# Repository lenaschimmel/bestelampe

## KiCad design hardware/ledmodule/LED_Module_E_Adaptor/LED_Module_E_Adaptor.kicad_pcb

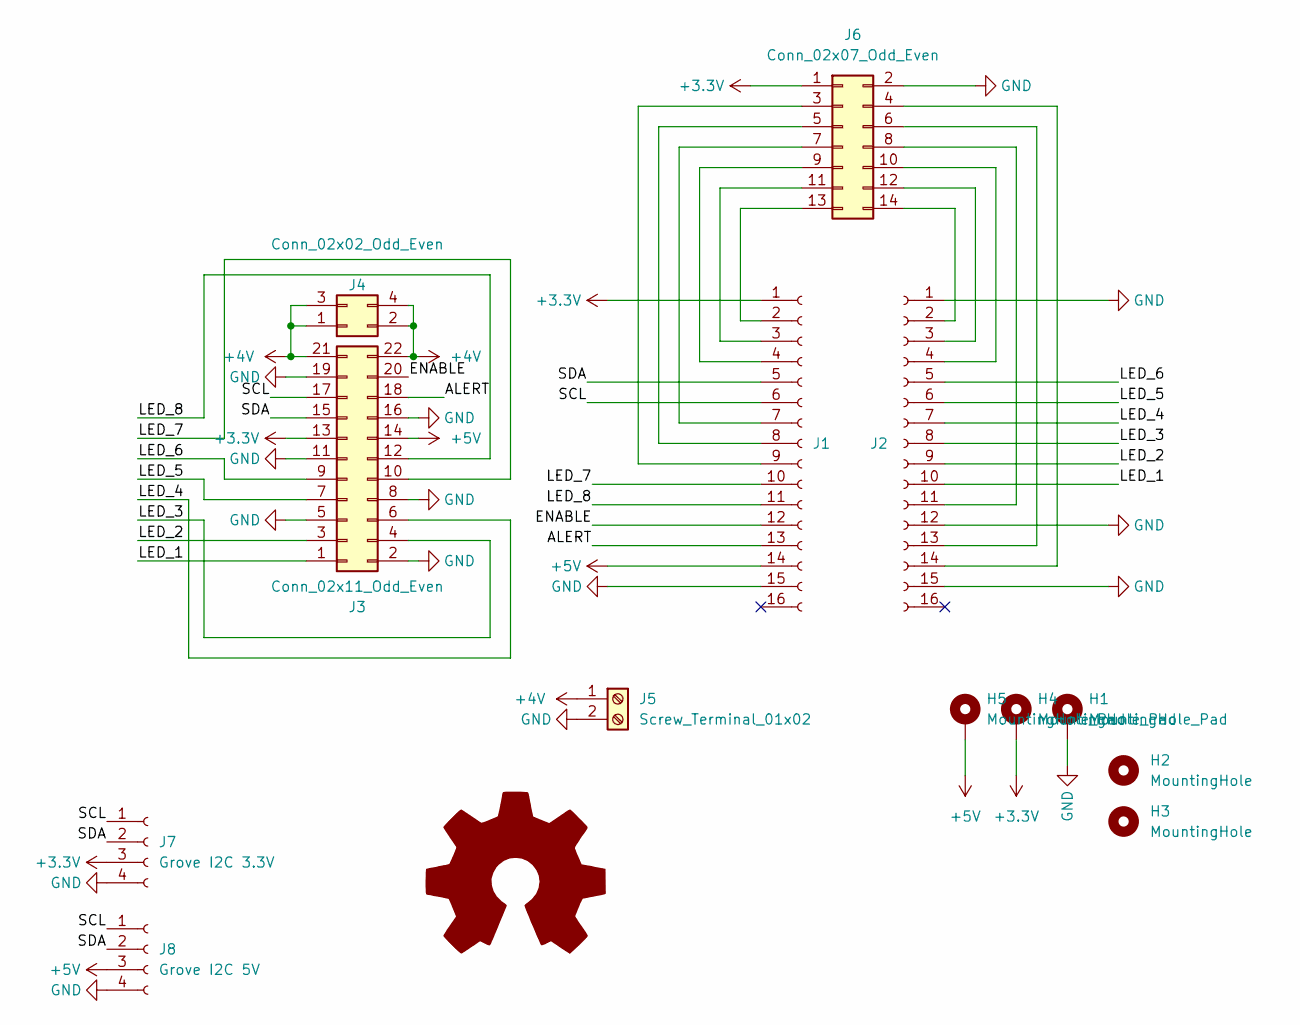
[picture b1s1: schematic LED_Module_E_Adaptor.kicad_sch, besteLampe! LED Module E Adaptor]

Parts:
H1, H4, H5: MountingHole_Pad; TestPoint_THTPad_D2.5mm_Drill1.2mm
H2, H3: MountingHole; MountingHole_3.2mm_M3
J1, J2: Conn_01x16_Socket; PinSocket_1x16_P2.54mm_Vertical
J3: Conn_02x11_Odd_Even; PinHeader_2x11_P2.54mm_Vertical
J4: Conn_02x02_Odd_Even; PinHeader_2x02_P2.54mm_Vertical
J5: Screw_Terminal_01x02; TerminalBlock_4Ucon_1x02_P3.50mm_Horizontal
J6: Conn_02x07_Odd_Even; PinHeader_2x07_P2.54mm_Vertical
J7: Grove I2C 3.3V; NS-Tech_Grove_1x04_P2mm_Vertical
J8: Grove I2C 5V; NS-Tech_Grove_1x04_P2mm_Vertical

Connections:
+3.3V: H4.1, J1.1, J3.13, J6.1, J7.3
+4V: J3.21, J3.22, J4.1, J4.2, J4.3, J4.4, J5.1
+5V: H5.1, J1.14, J3.14, J8.3
/ALERT: J1.13, J3.18
/ENABLE: J1.12, J3.20
/LED_1: J2.10, J3.1
/LED_2: J2.9, J3.3
/LED_3: J2.8, J3.4
/LED_4: J2.7, J3.6
/LED_5: J2.6, J3.7
/LED_6: J2.5, J3.9
/LED_7: J1.10, J3.10
/LED_8: J1.11, J3.12
/SCL: J1.6, J3.17, J7.1, J8.1
/SDA: J1.5, J3.15, J7.2, J8.2
GND: H1.1, J1.15, J2.1, J2.12, J2.15, J3.2, J3.5, J3.8, J3.11, J3.16, J3.19, J5.2, J6.2, J7.4, J8.4
unnamed: J1.2, J6.13
unnamed: J1.3, J6.11
unnamed: J1.4, J6.9
unnamed: J1.7, J6.7
unnamed: J1.8, J6.5
unnamed: J1.9, J6.3
unnamed: J2.2, J6.14
unnamed: J2.3, J6.12
unnamed: J2.4, J6.10
unnamed: J2.11, J6.8
unnamed: J2.13, J6.6
unnamed: J2.14, J6.4

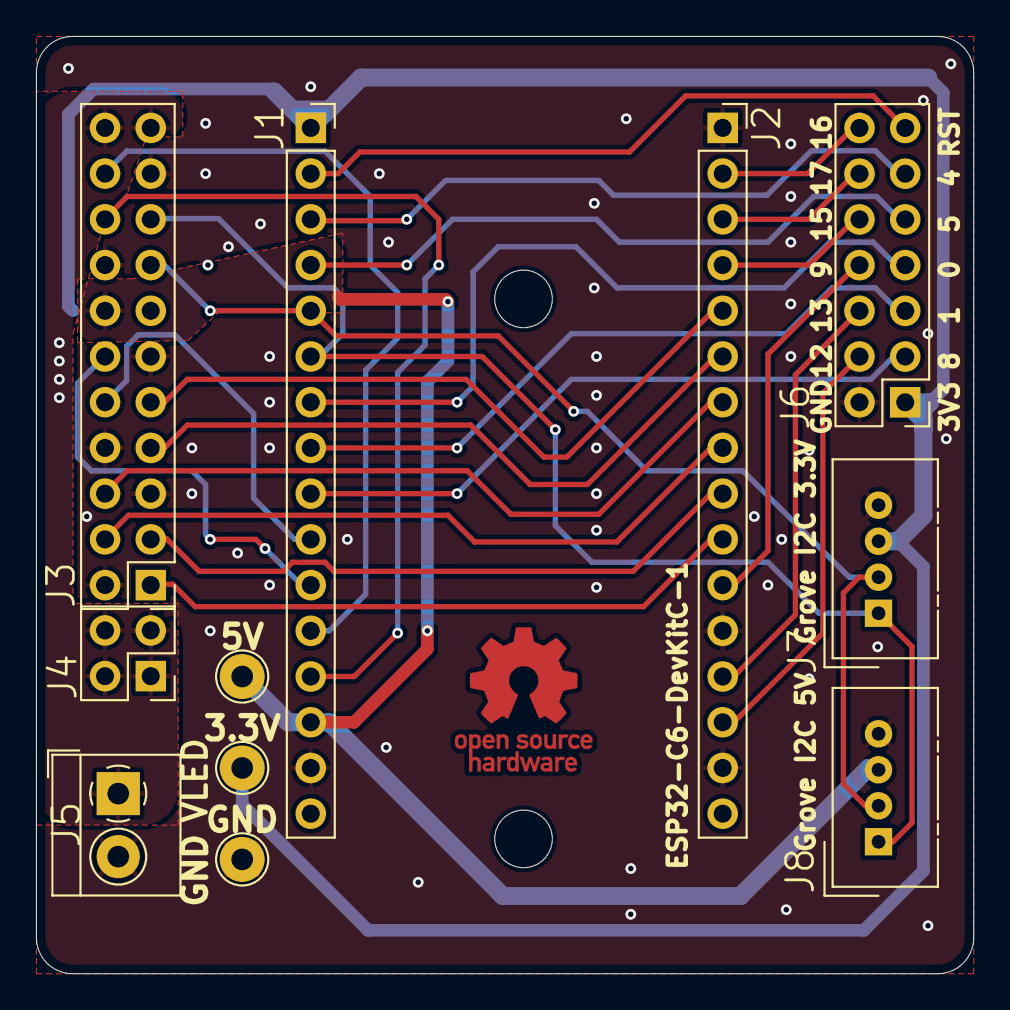
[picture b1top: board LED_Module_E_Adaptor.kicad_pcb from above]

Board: 2 copper layers, 52.1 x 52.1 mm, 13 parts (0 on the bottom side), 28 nets.

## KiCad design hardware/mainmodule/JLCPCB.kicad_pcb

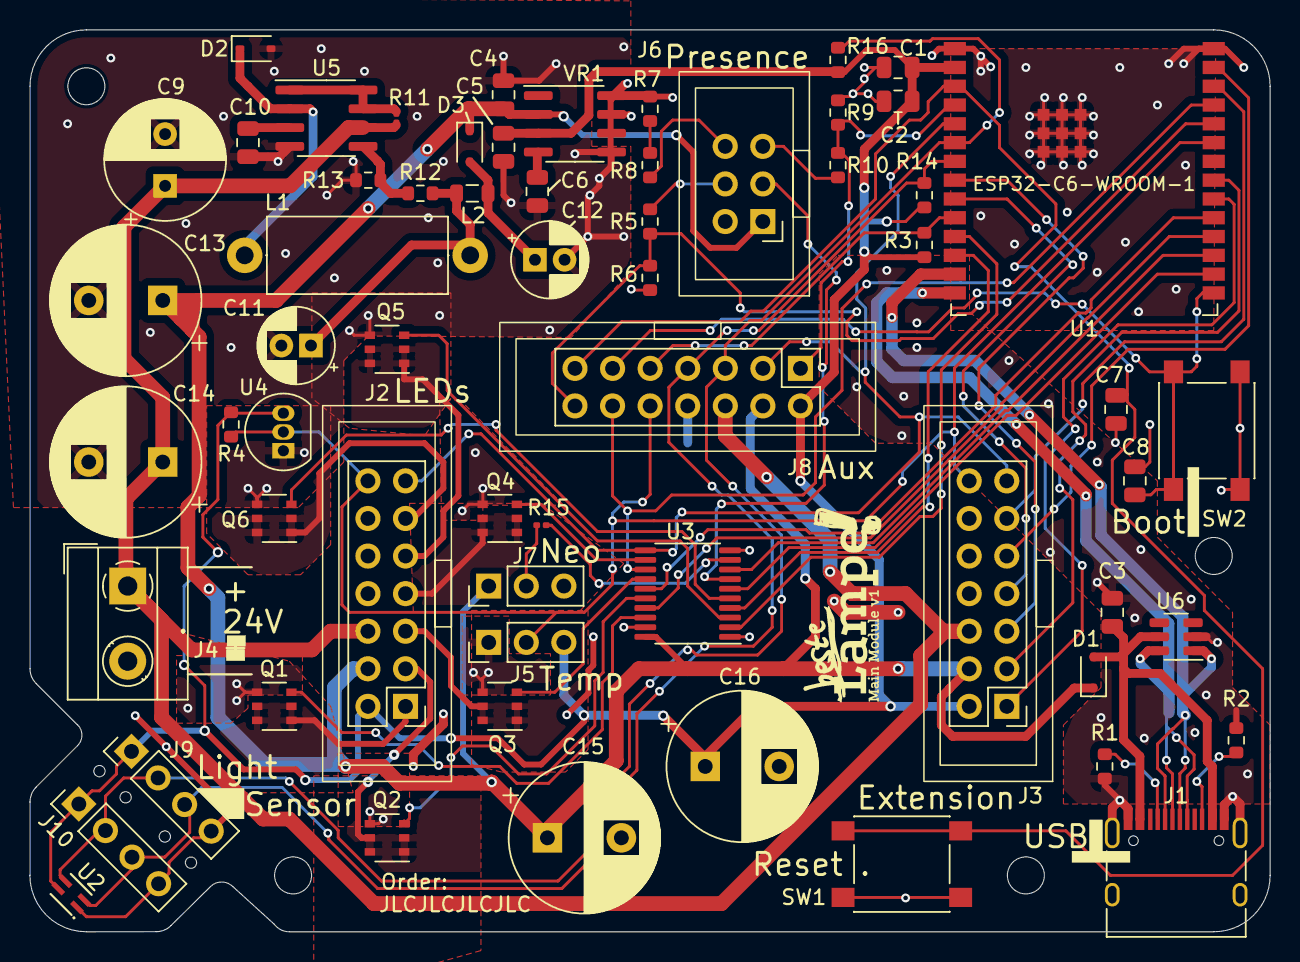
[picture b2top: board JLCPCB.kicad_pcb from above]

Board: 2 copper layers, 83.8 x 61.0 mm, 65 parts (0 on the bottom side), 57 nets.

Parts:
C1, C7, C8: 100n; C_0805_2012Metric
C2: 22u; C_0805_2012Metric
C3: 10u; C_0805_2012Metric
C4: 1u; C_0805_2012Metric
C5: 2u2; C_0805_2012Metric
C6: 10n; C_0805_2012Metric
C9: 100u; CP_Radial_D8.0mm_P3.50mm
C10: 470p; C_0805_2012Metric
C11: 2u2; CP_Radial_D5.0mm_P2.00mm
C12: 100u; CP_Radial_D5.0mm_P2.00mm
C13, C14, C15, C16: 470u; CP_Radial_D10.0mm_P5.00mm
D1, D2, D3: 1N5819; D_SOD-323
H1, H1#2, H1#3, H1#4: MountingHole; MountingHole_2.5mm
J1: USB+; USB_C_Receptacle_HRO_TYPE-C-31-M-12
J2: To LED_MOD_0; PinHeader_2x07_P2.54mm_Vertical_Boxed
J3: To EXT_MOD_1; PinHeader_2x07_P2.54mm_Vertical_Boxed
J4: V24_IN; TerminalBlock_MetzConnect_Type101_RT01602HBWC_1x02_P5.08mm_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
J5: Temp; PinHeader_1x03_P2.54mm_Vertical
J6: Presence; PinHeader_2x03_P2.54mm_Vertical_Boxed
J7: Neo; PinHeader_1x03_P2.54mm_Vertical
J8: AUX; PinHeader_2x07_P2.54mm_Vertical_Boxed
J9, J10: Conn_01x04; PinHeader_1x04_P2.54mm_Vertical
L1: 220u; L_Axial_L12.0mm_D5.0mm_P15.24mm_Horizontal_Fastron_MISC
L2: 1u; L_0805_2012Metric
Q1, Q2, Q3, Q4, Q5, Q6: Si3456DDV; TSOP-6_1.65x3.05mm_P0.95mm
R1, R2, R4, R5, R8, R10: 5K1; R_0603_1608Metric
R3, R6, R7, R9: 10K; R_0603_1608Metric
R11: 360m; R_0201_0603Metric
R12: 22k; R_0603_1608Metric
R13: 6k8; R_0603_1608Metric
R14, R16: 2k4; R_0603_1608Metric
R15: 470; R_0201_0603Metric
SW1, SW2: SW_Push; SW_Push_1P1T_NO_6x6mm_H9.5mm
U1: ESP32-C6-WROOM-1
U3: 74HCT244; TSSOP-20_4.4x6.5mm_P0.65mm
U4: DS18B20; TO-92_Inline
U5: MC34063AD; SOIC-8_3.9x4.9mm_P1.27mm
U6: DT1042-04SO1; TSOT-23-6
VR1: 3V3; SOIC-8_3.9x4.9mm_P1.27mm

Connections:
+3.3V: C1.1, C2.1, C5.1, C16.1, J2.2, J3.2, J5.3, J8.2, J9.1, J10.1, R3.2, R4.1, R14.2, R16.2, U1.2 (3V3), U4.3 (V_{DD}), VR1.3 (VOUT)
+5V: C4.1, C13.1, C15.1, D1.1 (K), D3.1 (K), J2.4, J3.4, J6.1, J7.1, J8.4, U3.20 (VCC), VR1.2 (VIN)
+24V: C9.1, C14.1, J2.6, J3.6, J4.1, J8.6, R11.1, U5.6 (Vin)
/BOOT8: J8.9, R3.1, U1.10 (GPIO8)
/BOOT9: C8.2, J8.11, SW2.2, U1.15 (GPIO9)
/CC1: J1.A5 (CC1), R1.1
/CC2: J1.B5 (CC2), R2.1
/CH0.1: U1.11 (GPIO10), U3.2 (1A0)
/CH0.2: U1.12 (GPIO11), U3.4 (1A1)
/CH0.3: U1.16 (GPIO18), U3.6 (1A2)
/CH0.4: U1.17 (GPIO19), U3.8 (1A3)
/CH0.5: U1.18 (GPIO20), U3.17 (2A0)
/CH0.6: U1.19 (GPIO21), U3.15 (2A1)
/D+: J1.A6 (D+), J1.B6 (D+), U1.14 (GPIO13/USB_D+), U6.6 (IO4)
/D-: J1.A7 (D-), J1.B7 (D-), U1.13 (GPIO12/USB_D-), U6.1 (IO1)
/DR0.1: Q1.3 (G), U3.18 (1Y0)
/DR0.2: Q2.3 (G), U3.16 (1Y1)
/DR0.3: Q3.3 (G), U3.14 (1Y2)
/DR0.4: Q4.3 (G), U3.12 (1Y3)
/DR0.5: Q5.3 (G), U3.3 (2Y0)
/DR0.6: Q6.3 (G), U3.5 (2Y1)
/DR_NEO: R15.2, U3.9 (2Y3)
/EN: C7.2, J8.13, SW1.2, U1.3 (EN/CHIP_PU)
/L0.1: J2.1, Q1.1 (D), Q1.2 (D), Q1.5 (D), Q1.6 (D)
/L0.2: J2.3, Q2.1 (D), Q2.2 (D), Q2.5 (D), Q2.6 (D)
/L0.3: J2.5, Q3.1 (D), Q3.2 (D), Q3.5 (D), Q3.6 (D)
/L0.4: J2.7, Q4.1 (D), Q4.2 (D), Q4.5 (D), Q4.6 (D)
/L0.5: J2.9, Q5.1 (D), Q5.2 (D), Q5.5 (D), Q5.6 (D)
/L0.6: J2.11, Q6.1 (D), Q6.2 (D), Q6.5 (D), Q6.6 (D)
/L1.1: J3.1, U1.20 (GPIO22)
/L1.2: J3.3, U1.21 (GPIO23)
/L1.3: J3.5, U1.8 (GPIO0/ADC1_CH0/XTAL_32K_P)
/L1.4: J3.7, U1.9 (GPIO1/ADC1_CH1/XTAL_32K_N)
/L1.5: J3.9, U1.27 (GPIO2/ADC1_CH2)
/L1.6: J3.11, U1.26 (GPIO3/ADC1_CH3)
/NEO: J2.13, J3.13, J8.3, U1.5 (MTDI/GPIO5/ADC1_CH5), U3.11 (2A3)
/PRES_A_3V3: J8.1, R9.1, R10.2, U1.4 (MTMS/GPIO4/ADC1_CH4)
/PRES_A_5V: J6.5, R10.1
/PRES_B_3V3: R7.1, R8.2
/PRES_B_5V: J6.6, R8.1
/PRES_RX_3V3: J8.14, R5.2, R6.1, U1.24 (U0RXD/GPIO17)
/PRES_RX_5V: J6.4, R5.1
/PRES_TX_3V3: J8.12, U1.25 (U0TXD/GPIO16), U3.13 (2A2)
/PRES_TX_5V: J6.3, U3.7 (2Y2)
/SCL: J8.5, J9.2, J10.2, R16.1, U1.6 (MTCK/GPIO6/ADC1_CH6)
/SDA: J8.7, J9.3, J10.3, R14.1, U1.7 (MTDO/GPIO7)
/TEMP: J2.14, J3.14, J5.2, J8.10, R4.2, U1.23 (GPIO15), U4.2 (DQ)
/VBUS: C3.1, D1.2 (A), J1.A4 (VBUS), J1.A9 (VBUS), J1.B4 (VBUS), J1.B9 (VBUS), U6.5 (VCC)
GND: C1.2, C2.2, C3.2, C4.2, C5.2, C6.2, C7.1, C8.1, C9.2, C10.2, C11.2, C12.2, C13.2, C14.2, C15.2, C16.2, D2.2 (A), J1.A1 (GND), J1.A12 (GND), J1.B1 (GND), J1.B12 (GND), J1.S1 (SHIELD), J2.8, J2.10, J2.12, J3.8, J3.10, J3.12, J4.2, J5.1, J6.2, J7.3, J8.8, J9.4, J10.4, Q1.4 (S), Q2.4 (S), Q3.4 (S), Q4.4 (S), Q5.4 (S), Q6.4 (S), R1.2, R2.2, R6.2, R7.2, R9.2, R13.1, SW1.1, SW2.1, U1.1 (GND), U1.28 (GND), U1.29 (GND), U3.1 (1OE), U3.10 (GND), U3.19 (2OE), U4.1 (GND), U5.4 (GND), U6.2 (VSS), VR1.5 (GND), VR1.6 (GND), VR1.7 (GND), VR1.8 (GND)
unnamed: C11.1, L1.2, L2.1, R12.2
unnamed: D2.1 (K), L1.1, U5.2 (SwE)
unnamed: C12.1, D3.2 (A), L2.2
unnamed: J7.2, R15.1
unnamed: R11.2, U5.1 (SwC), U5.7 (Ipk), U5.8 (DC)
unnamed: C10.1, U5.3 (TC)
unnamed: R12.1, R13.2, U5.5 (Vfb)
unnamed: C6.1, VR1.4 (BYP)

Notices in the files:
hardware/ledmodule/LED_Module_E_Adaptor/LED_Module_E_Adaptor.kicad_pcb:
This source describes Open Hardware and is licensed under the CERN-OHL-S v2.
Copyright 2024 Lena Schimmel
